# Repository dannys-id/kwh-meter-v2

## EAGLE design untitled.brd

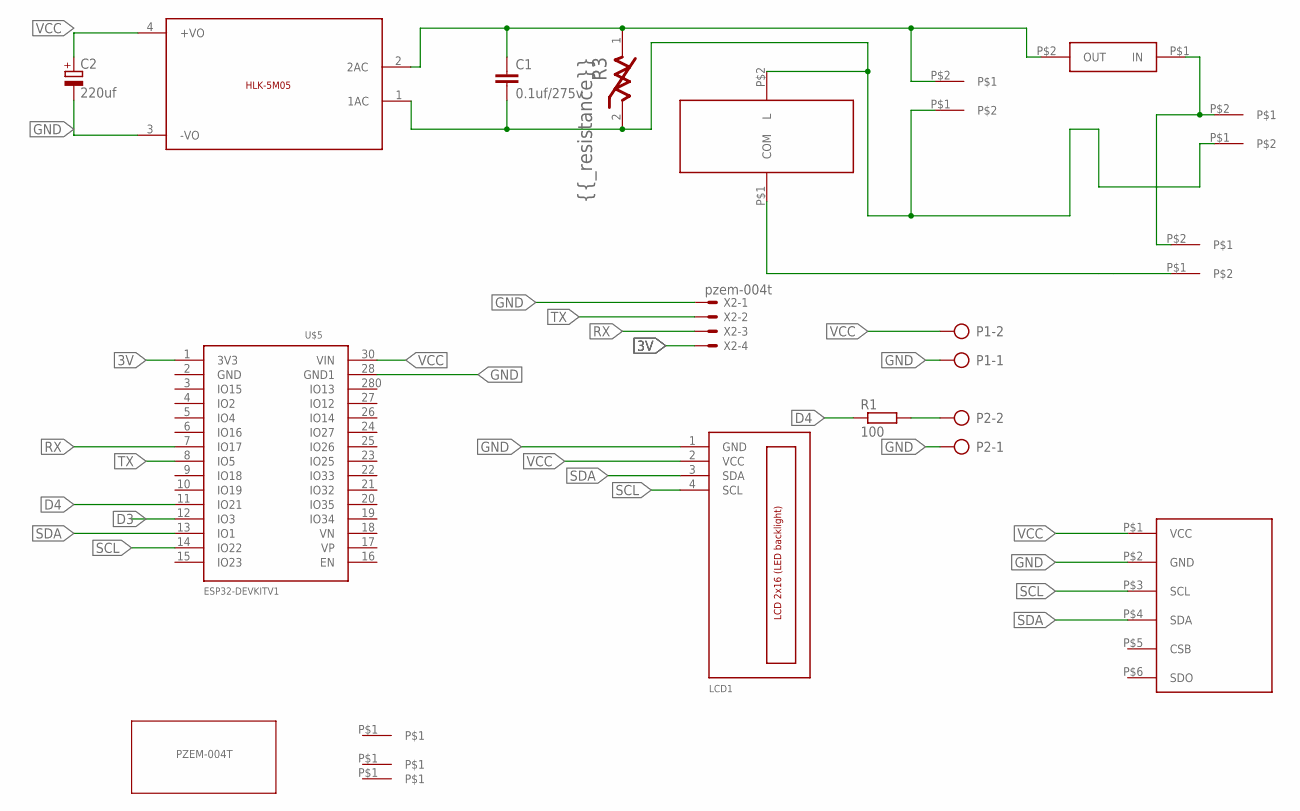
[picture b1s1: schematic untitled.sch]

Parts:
1, 220: KF76
BME280: BMP180; BPM180
C1: 0.1uf/275v; C7.5B5
C2: 220uf; E2-5
LCD1: LCD_2X16_SIL; HY-1602F
P1, P2: AK500/2-H
PZEM: KF76
R1: 100; 0207/12
R3: 10D561K; BOURNS_INC_MOV-10D471K_0
U$1: 5VDC/5W; HLK-5M05
U$2: TOROID
U$3: PZEM; PZEM_FOOTPRINT
U$4, U$6, U$7: SAPCER; SPACER
U$5: ESP32DEVKITV1; ESP32-DEVKITV1
U$8: FUSE
X2: pzem-004t; 22-23-2041

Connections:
3V: U$5.1 (3V3), X2.4
D3: U$5.12 (IO3)
D4: R1.1, U$5.11 (IO21)
GND: BME280.P$2 (GND), C2.-, LCD1.1 (GND), P1.1, P2.1, U$1.3 (-VO), U$5.28 (GND1), X2.1
unnamed: P2.2, R1.2
unnamed: 1.P$1, U$2.P$1 (COM)
unnamed: C1.1, PZEM.P$2, R3.1, U$1.2 (2AC), U$8.P$2 (OUT)
unnamed: 1.P$2, 220.P$2, U$8.P$1 (IN)
unnamed: 220.P$1, C1.2, PZEM.P$1, R3.2, U$1.1 (1AC), U$2.P$2 (L)
RX: U$5.7 (IO17), X2.3
SCL: BME280.P$3 (SCL), LCD1.4 (SCL), U$5.14 (IO22)
SDA: BME280.P$4 (SDA), LCD1.3 (SDA), U$5.13 (IO1)
TX: U$5.8 (IO5), X2.2
VCC: BME280.P$1 (VCC), C2.+, LCD1.2 (VCC), P1.2, U$1.4 (+VO), U$5.30 (VIN)

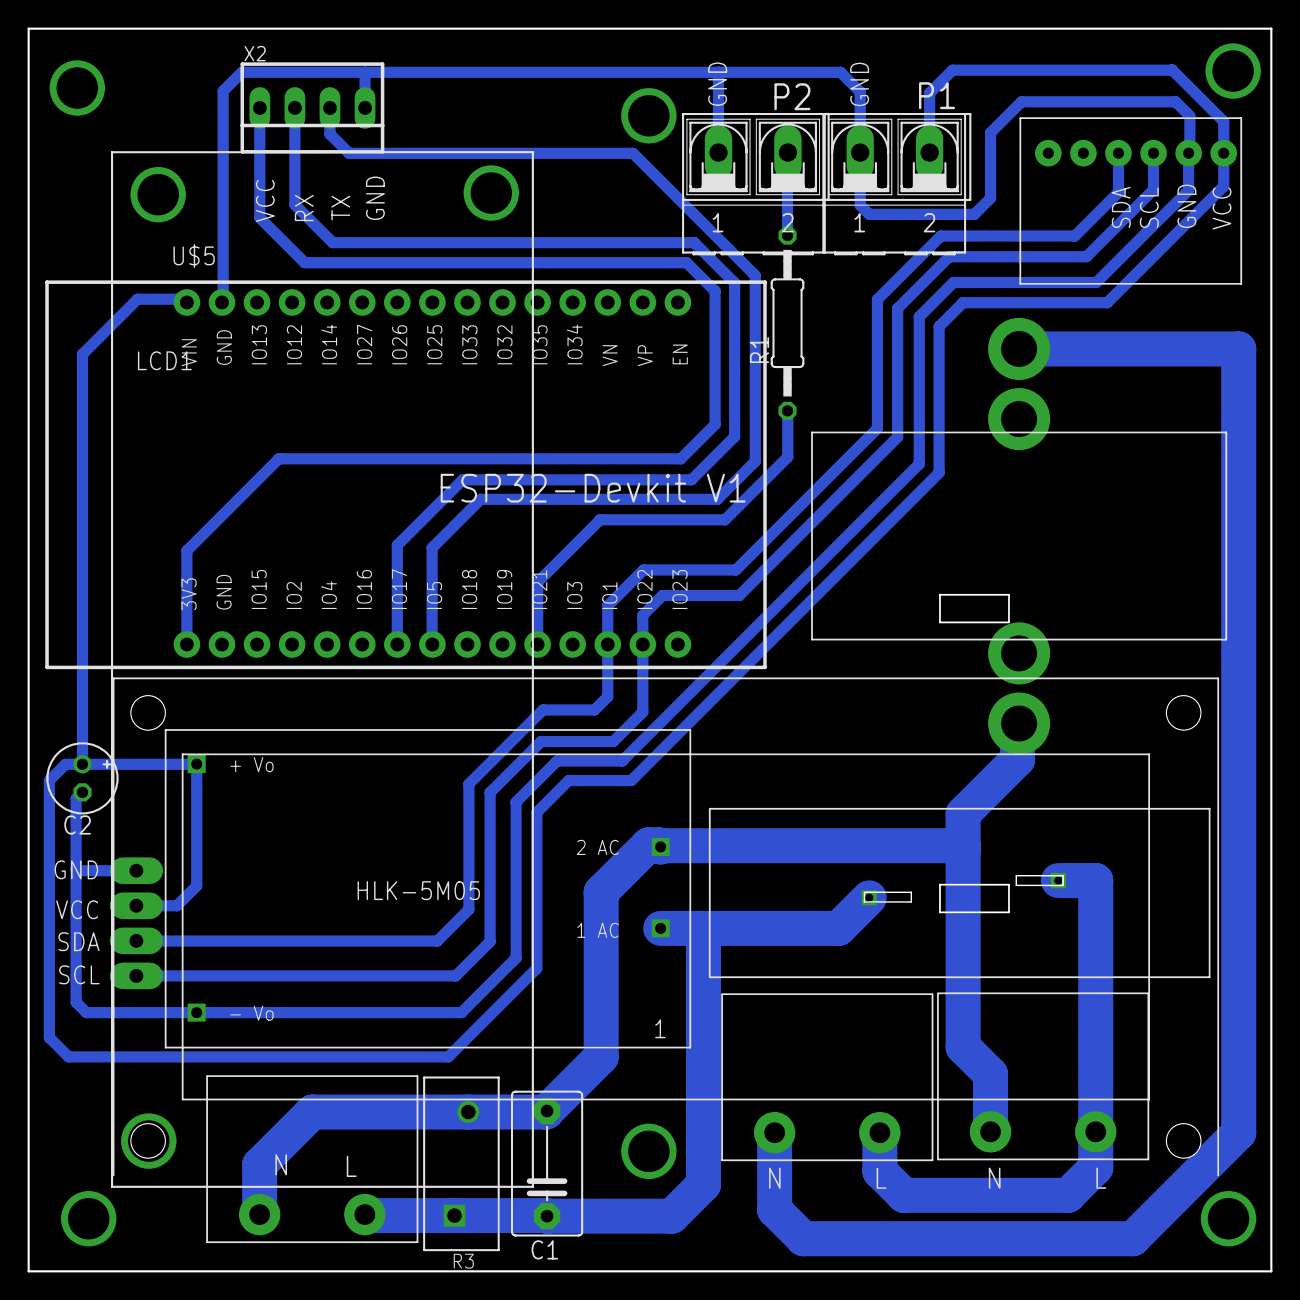
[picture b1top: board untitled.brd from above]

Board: 2 copper layers, 90.0 x 90.0 mm, 20 parts (0 on the bottom side), 13 nets.

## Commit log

2022-12-26 comit
    comit
2022-12-26 hapus gambar
2022-12-27 0021
2022-12-28 2158
